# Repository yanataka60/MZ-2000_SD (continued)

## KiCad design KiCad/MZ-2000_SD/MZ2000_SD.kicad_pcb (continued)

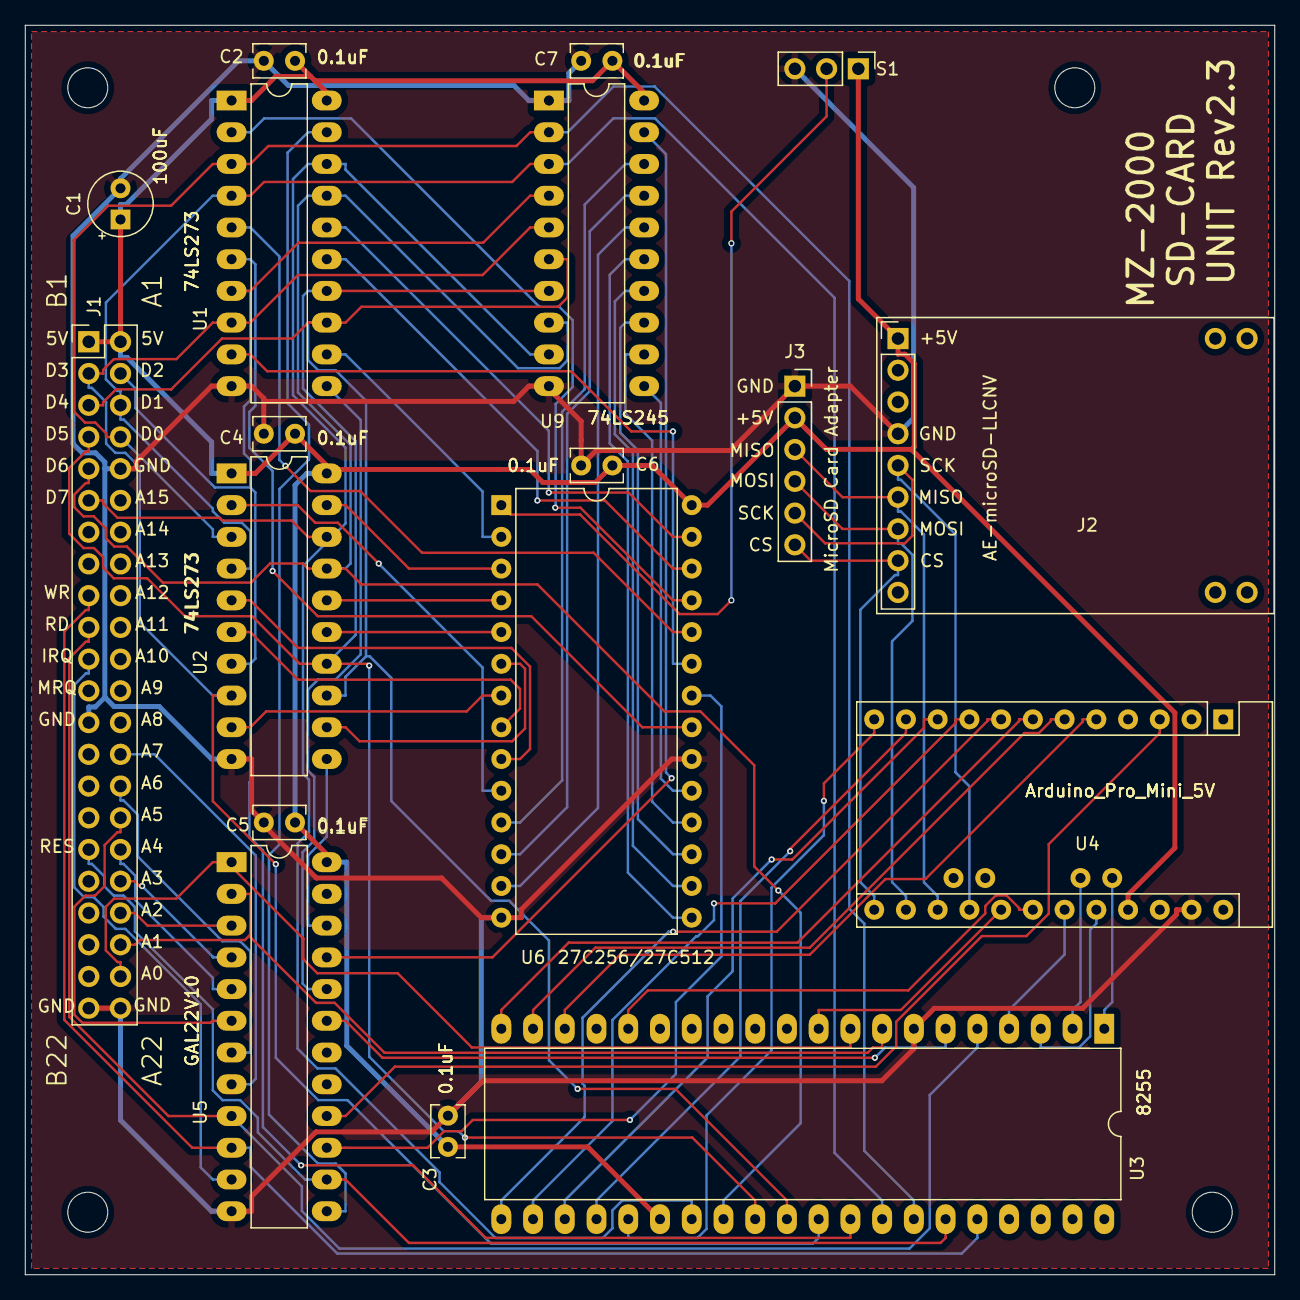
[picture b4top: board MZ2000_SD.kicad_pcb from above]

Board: 2 copper layers, 100.0 x 100.0 mm, 22 parts (0 on the bottom side), 71 nets.

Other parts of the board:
MH1, MH2, MH3, MH4: MountingHole_3.2mm_M3
